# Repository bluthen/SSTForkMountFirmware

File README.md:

# SST Forkmount

This repo contains the electronic designs and software for [StarSync Trackers](https://starsynctrackers.com/)
computerized forkmount equatorial mounts. It was designed to work with SST hardware but should work with any fork mount
that uses steppers for motors.

## Component Structure

Below it tries to describe

* Computer connects to the mount through Ethernet or Wifi and control the telescope in one of the following ways.
    * A web browser [SST Discovery Tool](https://github.com/bluthen/SSTForkMountDiscovery)
    * software capable of communicating through a LX200 protocol
* Handpad is a device attached through a USB cable
    * It has a GPS moduled embedded inside it that can give the telescope accurate time and location.
    * Has a interface to control the telescope without a computer attached, with goto and manual slew functions.
* Raspberry pi has a controller board (Pi Hat) attached to it and has three main components.
    * Flask API Server - Provides a REST like API to control the telescope
    * React MUI Frontend - web based user interface to communcate with the API Server
    * LX200 Compatible TCPIP Server - An alternative way to control the telescope through a dedicated TCP/IP Port.
* Motor Control Chain
    * Microcontroller (Teensy) - The Raspberry pi has a controller board attached and communicates with it through TTL
      Serial.
    * The Microcontroller (Teensy) - communicates with stepper drivers using SPI Protocol and step/direction protocol.
    * The stepper drivers (TMC5160) - controls the RA/Dec steppers to point the telescope

# Project directory structure

* [electronics](electronics) - Files related to the hardware of: Handpad, serial to ethernet, main controller
    * [enclosures](electronics/enclosures) - Enclosures to house electronics
    * [firmware](electronics/firmware) - Microcontroller firmware
    * [pcb](electronics/pcb) - Schematic and PCB files
* [piside](piside) - Software the run on the Pi.
    * [client_advanced_slew_limits](piside/client_advanced_slew_limits) - Slew limits UI component
    * [client_main](pisiude/client_main) - The Material UI web client
    * [server](piside/server) - Flask API Server

# TODOs

* Improve a test Error modeling
    * Add Star Alignment to handpad that uses the error modeling feature
    * Good prompts for error modeling/alignment to web ui
* Script and instructions to generate object and city elevation database `ssteq.sqlite`
* More python type-hinting
* Switch from Flask to [FastAPI](https://fastapi.tiangolo.com/)
* Cleanup files piside/server in director submodules
* Better testing of encoder usage
* Easier pi setup
* Instructions for settings.json for docker usage
* Alt/Az Mode

# Screenshots

Screen shots of the web client.

# Related projects

If you are interested in this project, some of these other open source projects might interest you.

* [OnStep](https://github.com/hjd1964/OnStep)
* [AstroEQ](https://www.astroeq.co.uk/)
* [TeenAstro](https://groups.io/g/TeenAstro)

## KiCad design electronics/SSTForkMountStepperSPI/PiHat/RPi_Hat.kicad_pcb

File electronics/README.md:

# SST Electronics Hardware

## PiHat/SSTFork Stepper Micro

This is the electronics that take communication from the Pi and control the stepper motors.

## Handpad

This is the electronics of the handpad. A handheld device, with a display, to control the telescope mount.

## Serial to Ethernet

This is a small device that creates a serial port on the host computer and sends back and forth all communication on the
serial port to a IP_ADDRESS:Port through Ethernet.

This could be handy for older software that can only communicate with LX200 Protocol through a serial port.

**Computer** <-USB Serial-> **serial_to_ethernet** <-Ethernet-> **Device/Fork Mount**

# Directroy Structure

See each section for more information.

* [enclosures](enclosures) - Enclosure to house electronics
* [firmware](firmware) - Microcontroller firmware files
* [pcb](pcb) - Schematic and PCB for electronics

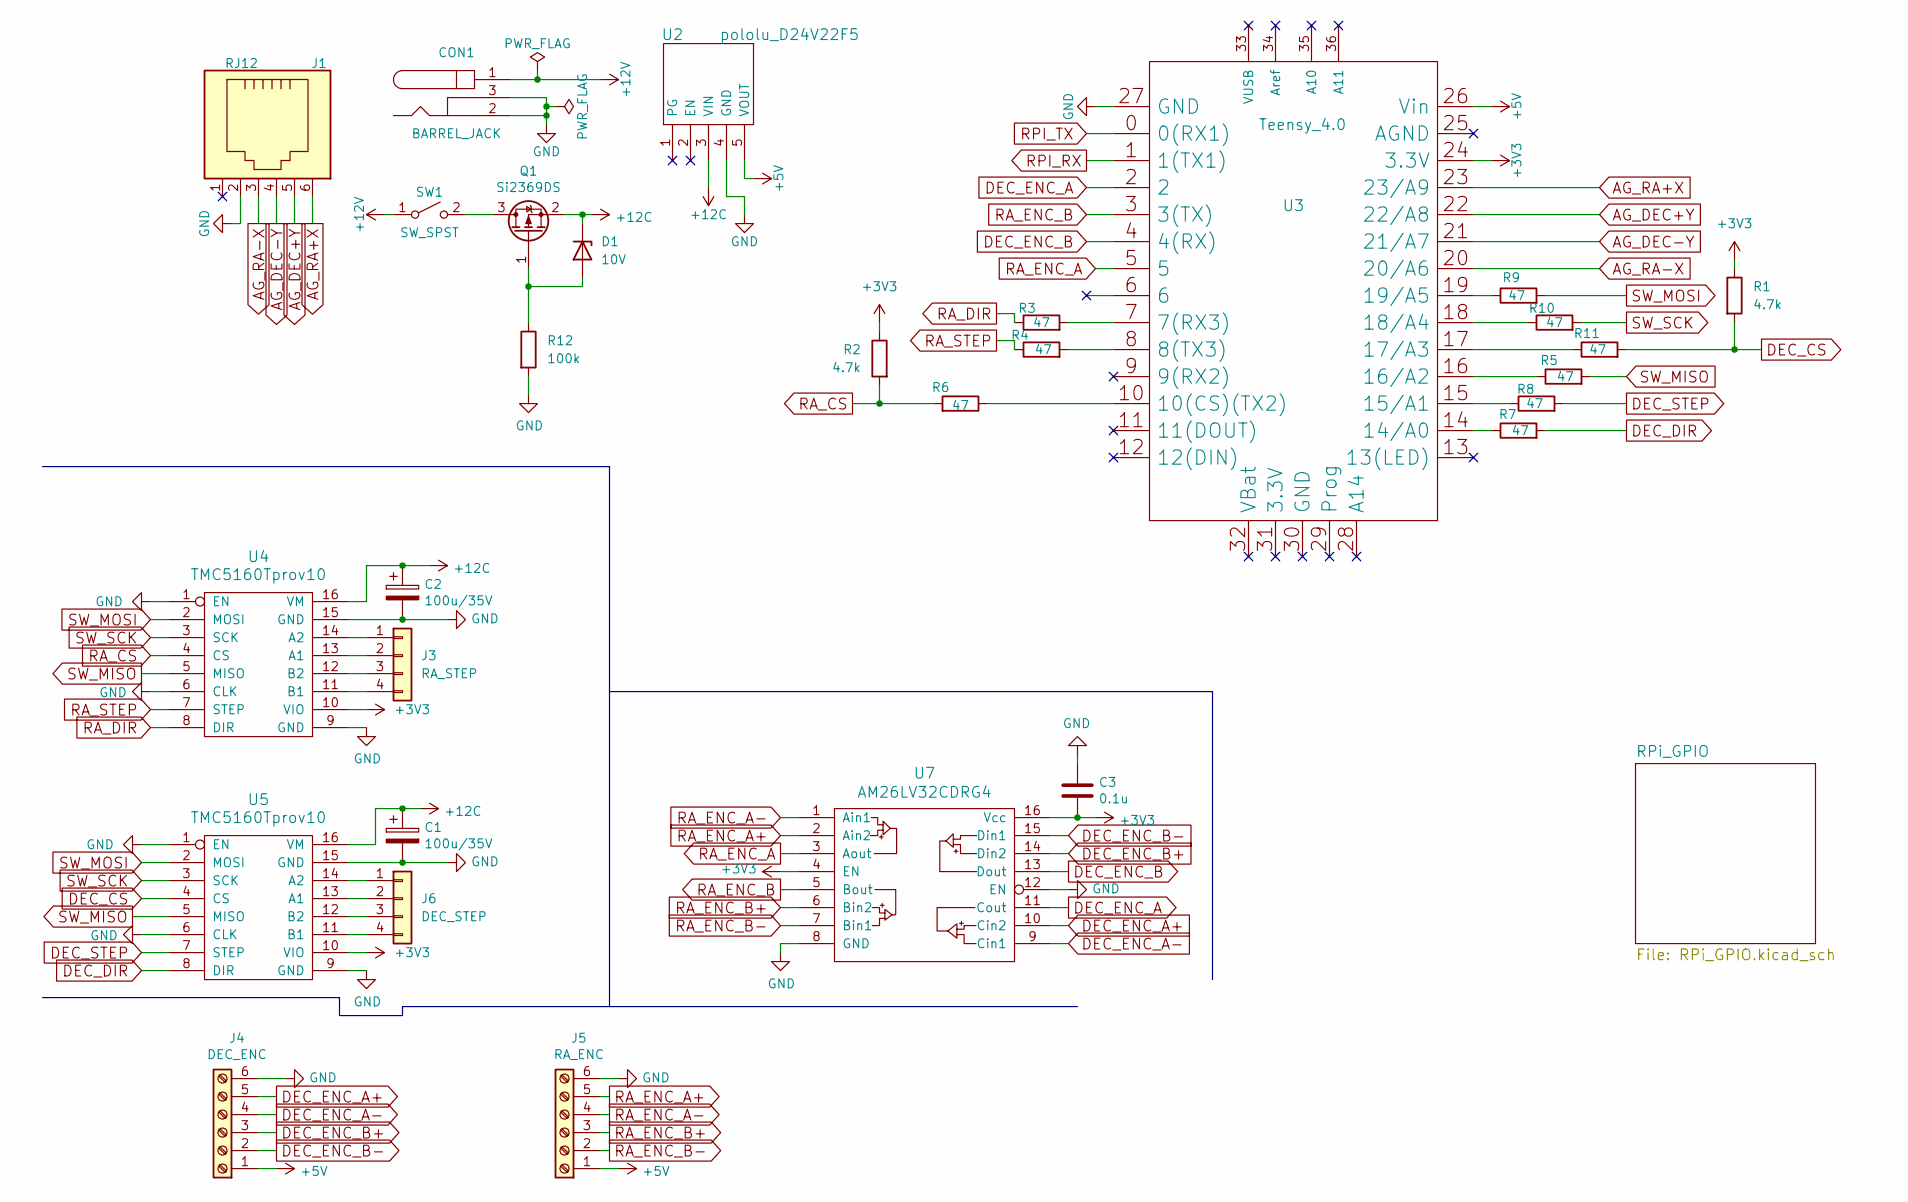
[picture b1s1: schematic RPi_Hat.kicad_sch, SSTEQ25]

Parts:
C1, C2: 100u/35V; CP_Radial_D6.3mm_P2.50mm
C3: 0.1u; C_0603
CON1: BARREL_JACK; POWER_JACK_PTH
D1: 10V; D_SOD-123
J1: RJ12; RJ11-6
J3: RA_STEP; JST_XH_B4B-XH-A_1x04_P2.50mm_Vertical
J4: DEC_ENC; JST_XH_B6B-XH-A_1x06_P2.50mm_Vertical
J5: RA_ENC; JST_XH_B6B-XH-A_1x06_P2.50mm_Vertical
J6: DEC_STEP; JST_XH_B4B-XH-A_1x04_P2.50mm_Vertical
Q1: Si2369DS; SOT-23
R1, R2: 4.7k; R_0603_1608Metric
R3, R4, R5, R6, R7, R8, R9, R10, R11: 47; R_0603_1608Metric
R12: 100k; R_0603_1608Metric
SW1: SW_SPST; PWR_SWITCH_RA1H1C112R
U2: pololu_D24V22F5
U3: Teensy_4.0; Teensy-3.1
U4, U5: TMC5160Tprov10; pololu_a4988
U7: AM26LV32CDRG4; SOIC-16_3.9x9.9mm_Pitch1.27mm

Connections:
+3V3: C3.2, R1.1, R2.1, U3.24 (3.3V), U4.10 (VIO), U5.10 (VIO), U7.4 (EN), U7.16 (Vcc)
+5V: J4.1, J5.1, U2.5 (VOUT), U3.26 (Vin); also elsewhere on the board
+12C: C1.1, C2.1, D1.1 (K), Q1.2 (S), U2.3 (VIN), U4.16 (VM), U5.16 (VM)
+12V: CON1.1, SW1.1 (A)
AG_DEC+Y: J1.5, U3.22 (22/A8)
AG_DEC-Y: J1.4, U3.21 (21/A7)
AG_RA+X: J1.6, U3.23 (23/A9)
AG_RA-X: J1.3, U3.20 (20/A6)
DEC_CS: R1.2, R11.2, U5.4 (CS)
DEC_DIR: R7.2, U5.8 (DIR)
DEC_ENC_A: U3.2, U7.11 (Cout)
DEC_ENC_A+: J4.5, U7.10 (Cin2)
DEC_ENC_A-: J4.4, U7.9 (Cin1)
DEC_ENC_B: U3.4 (4(RX)), U7.13 (Dout)
DEC_ENC_B+: J4.3, U7.14 (Din2)
DEC_ENC_B-: J4.2, U7.15 (Din1)
DEC_STEP: R8.2, U5.7 (STEP)
GND: C1.2, C2.2, C3.1, CON1.2, CON1.3, J1.2, J4.6, J5.6, R12.2, U2.4 (GND), U3.27 (GND), U4.1 (EN), U4.6 (CLK), U4.9 (GND), U4.15 (GND), U5.1 (EN), U5.6 (CLK), U5.9 (GND), U5.15 (GND), U7.8 (GND), U7.12 (EN); also elsewhere on the board
unnamed: D1.2 (A), Q1.1 (G), R12.1
unnamed: J3.1, U4.14 (A2)
unnamed: J3.2, U4.13 (A1)
unnamed: J3.3, U4.12 (B2)
unnamed: J3.4, U4.11 (B1)
unnamed: J6.1, U5.14 (A2)
unnamed: J6.2, U5.13 (A1)
unnamed: J6.3, U5.12 (B2)
unnamed: J6.4, U5.11 (B1)
unnamed: Q1.3 (D), SW1.2 (B)
unnamed: R3.2, U3.7 (7(RX3))
unnamed: R4.2, U3.8 (8(TX3))
unnamed: R6.1, U3.10 (10(CS)(TX2))
unnamed: R7.1, U3.14 (14/A0)
unnamed: R8.1, U3.15 (15/A1)
unnamed: R5.1, U3.16 (16/A2)
unnamed: R11.1, U3.17 (17/A3)
unnamed: R10.1, U3.18 (18/A4)
unnamed: R9.1, U3.19 (19/A5)
RA_CS: R2.2, R6.2, U4.4 (CS)
RA_DIR: R3.1, U4.8 (DIR)
RA_ENC_A: U3.5, U7.3 (Aout)
RA_ENC_A+: J5.5, U7.2 (Ain2)
RA_ENC_A-: J5.4, U7.1 (Ain1)
RA_ENC_B: U3.3 (3(TX)), U7.5 (Bout)
RA_ENC_B+: J5.3, U7.6 (Bin2)
RA_ENC_B-: J5.2, U7.7 (Bin1)
RA_STEP: R4.1, U4.7 (STEP)
RPI_RX: U3.1 (1(TX1)); also elsewhere on the board
RPI_TX: U3.0 (0(RX1)); also elsewhere on the board
SW_MISO: R5.2, U4.5 (MISO), U5.5 (MISO)
SW_MOSI: R9.2, U4.2 (MOSI), U5.2 (MOSI)
SW_SCK: R10.2, U4.3 (SCK), U5.3 (SCK)

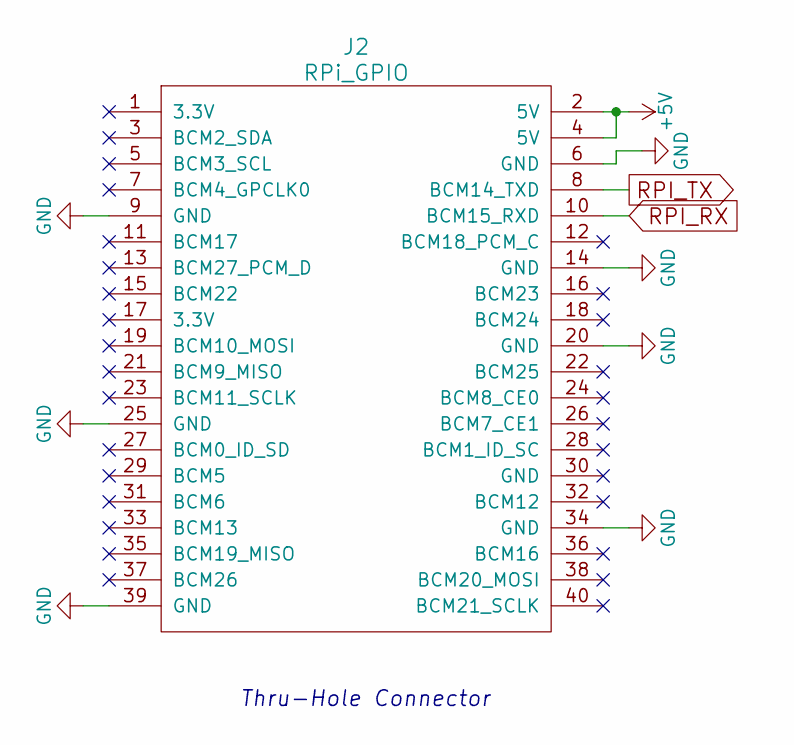
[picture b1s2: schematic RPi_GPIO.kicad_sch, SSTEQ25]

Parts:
J2: RPi_GPIO; Pin_Header_Straight_2x20

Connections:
+5V: J2.2 (5V), J2.4 (5V); also elsewhere on the board
GND: J2.6 (GND), J2.9 (GND), J2.14 (GND), J2.20 (GND), J2.25 (GND), J2.34 (GND), J2.39 (GND); also elsewhere on the board
RPI_RX: J2.10 (BCM15_RXD); also elsewhere on the board
RPI_TX: J2.8 (BCM14_TXD); also elsewhere on the board

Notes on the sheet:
Thru-Hole Connector

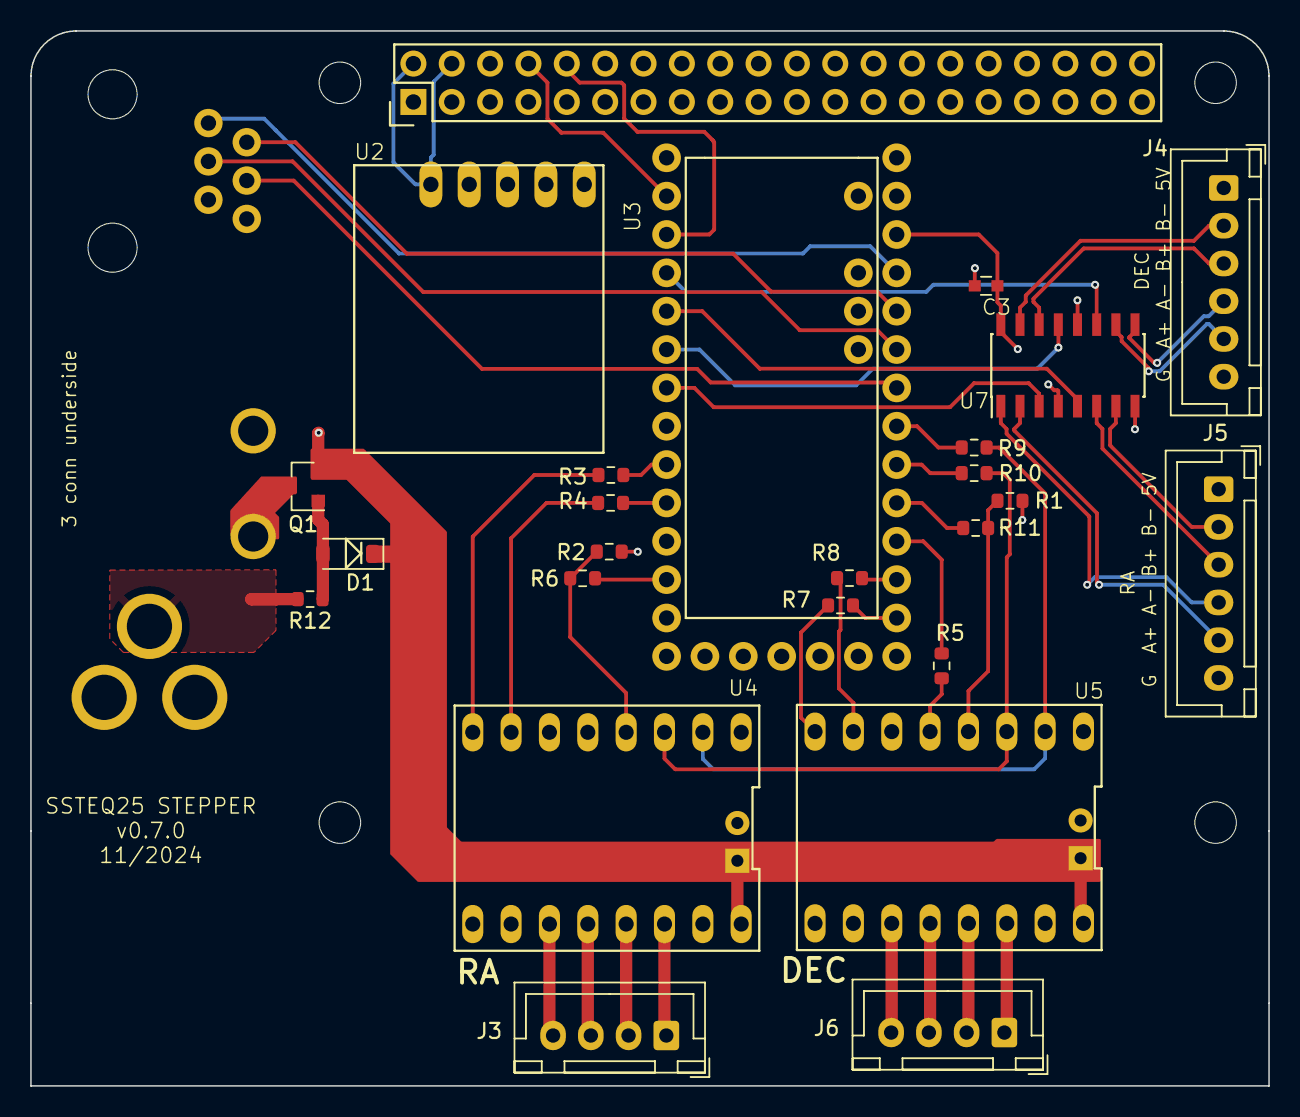
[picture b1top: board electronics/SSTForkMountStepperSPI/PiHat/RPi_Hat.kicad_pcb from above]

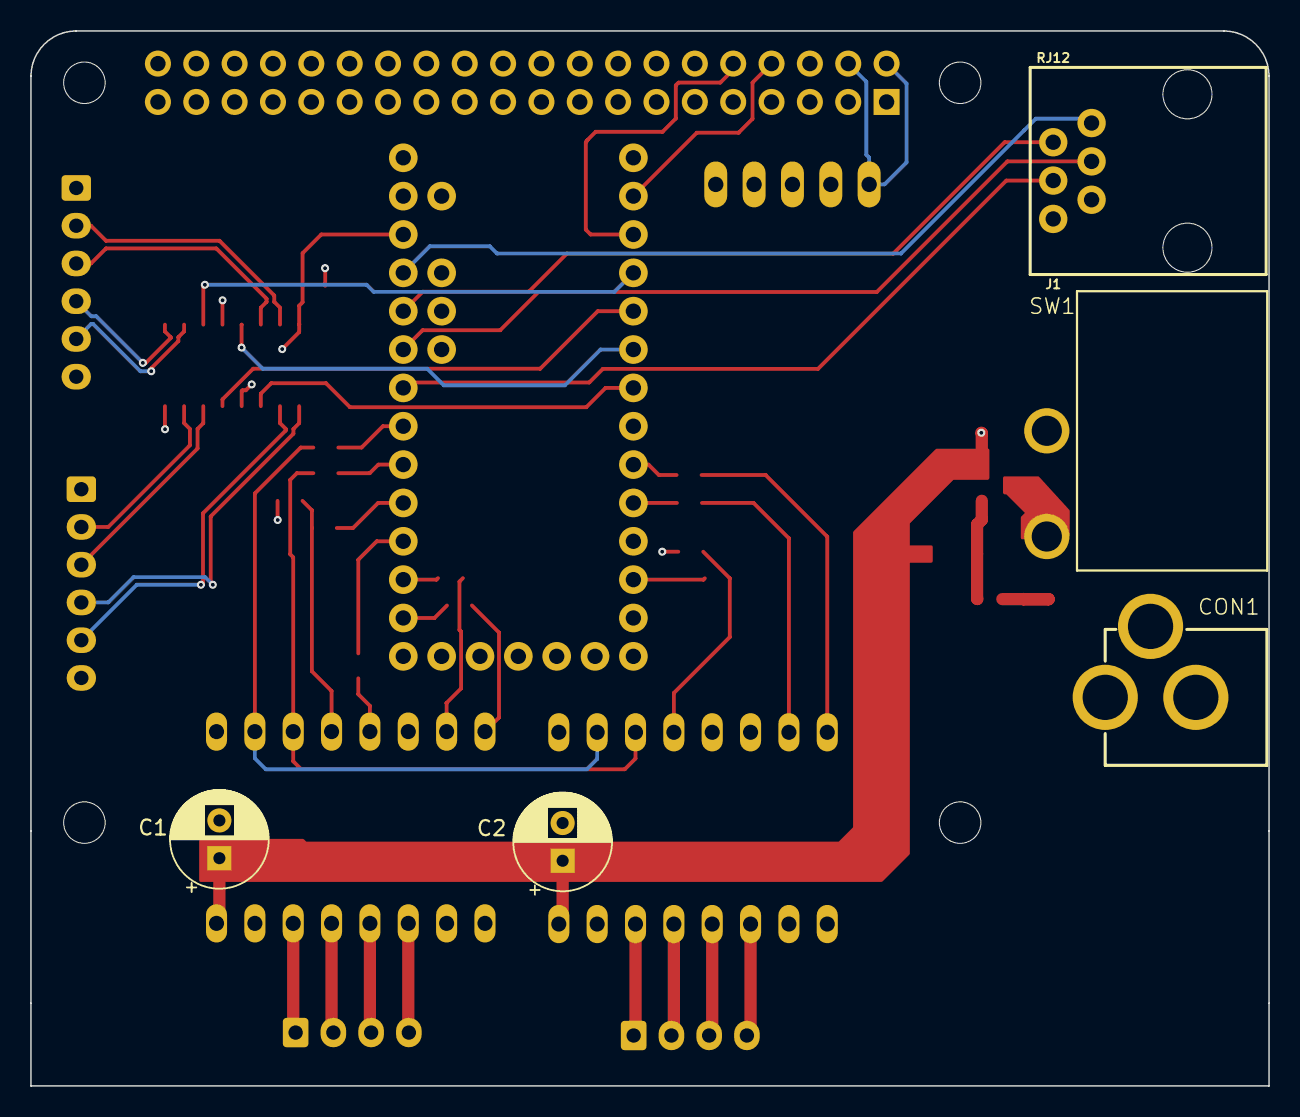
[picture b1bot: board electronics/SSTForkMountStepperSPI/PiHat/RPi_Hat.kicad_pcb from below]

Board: 4 copper layers, 82.0 x 69.9 mm, 30 parts (5 on the bottom side), 51 nets.

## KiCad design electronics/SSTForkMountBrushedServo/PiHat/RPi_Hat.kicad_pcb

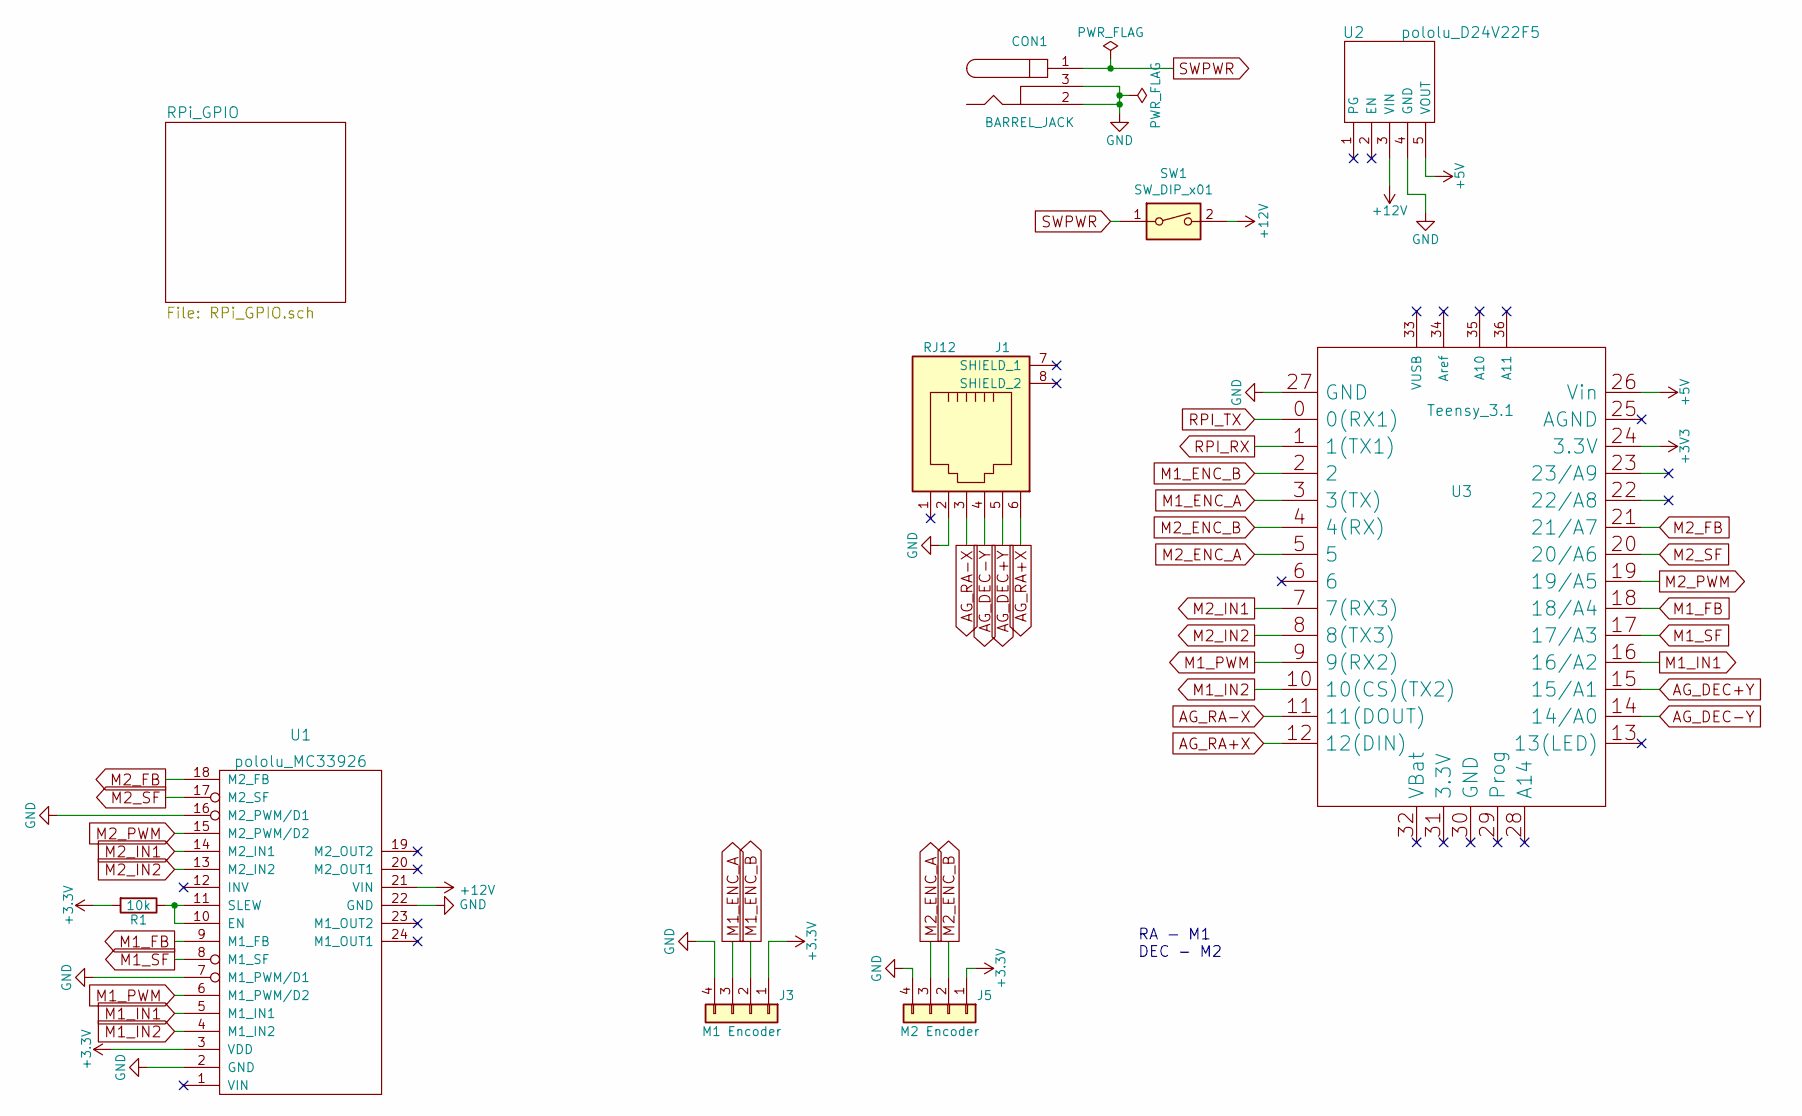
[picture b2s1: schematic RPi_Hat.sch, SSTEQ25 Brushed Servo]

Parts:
CON1: BARREL_JACK; POWER_JACK_PTH
J1: RJ12; RJ11-6
J3: M1 Encoder; 1X04_LOCK_LONGPADS
J5: M2 Encoder; 1X04_LOCK_LONGPADS
R1: 10k; R_0603
SW1: SW_DIP_x01; PWR_SWITCH_RA1H1C112R
U1: pololu_MC33926; pololu_mc33926
U2: pololu_D24V22F5
U3: Teensy_3.1; Teensy-3.1

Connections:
+5V: U2.5 (VOUT), U3.26 (Vin); also elsewhere on the board
+12V: SW1.2, U1.21 (VIN), U2.3 (VIN)
AG_DEC+Y: J1.5, U3.15 (15/A1)
AG_DEC-Y: J1.4, U3.14 (14/A0)
AG_RA+X: J1.6, U3.12 (12(DIN))
AG_RA-X: J1.3, U3.11 (11(DOUT))
GND: CON1.2, CON1.3, J1.2, J3.4, J5.4, U1.2 (GND), U1.7 (M1_PWM/D1), U1.16 (M2_PWM/D1), U1.22 (GND), U2.4 (GND), U3.27 (GND); also elsewhere on the board
M1_ENC_A: J3.3, U3.3 (3(TX))
M1_ENC_B: J3.2, U3.2
M1_FB: U1.9 (M1_FB), U3.18 (18/A4)
M1_IN1: U1.5 (M1_IN1), U3.16 (16/A2)
M1_IN2: U1.4 (M1_IN2), U3.10 (10(CS)(TX2))
M1_PWM: U1.6 (M1_PWM/D2), U3.9 (9(RX2))
M1_SF: U1.8 (M1_SF), U3.17 (17/A3)
M2_ENC_A: J5.3, U3.5
M2_ENC_B: J5.2, U3.4 (4(RX))
M2_FB: U1.18 (M2_FB), U3.21 (21/A7)
M2_IN1: U1.14 (M2_IN1), U3.7 (7(RX3))
M2_IN2: U1.13 (M2_IN2), U3.8 (8(TX3))
M2_PWM: U1.15 (M2_PWM/D2), U3.19 (19/A5)
M2_SF: U1.17 (M2_SF), U3.20 (20/A6)
unnamed: R1.1, U1.10 (EN), U1.11 (SLEW)
RPI_RX: U3.1 (1(TX1)); also elsewhere on the board
RPI_TX: U3.0 (0(RX1)); also elsewhere on the board
SWPWR: CON1.1, SW1.1

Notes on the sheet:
RA - M1 DEC - M2

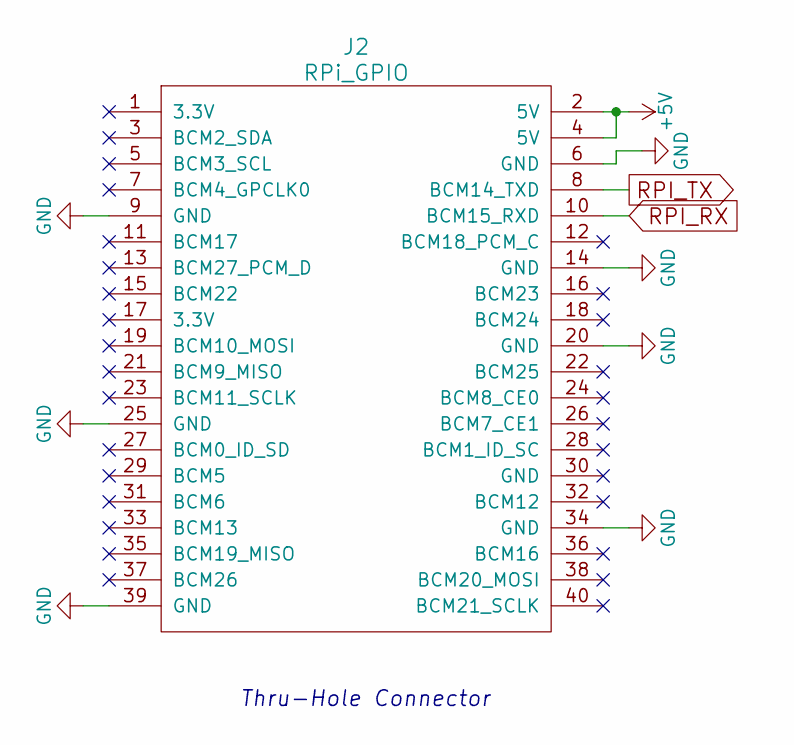
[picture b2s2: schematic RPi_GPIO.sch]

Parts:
J2: RPi_GPIO; Pin_Header_Straight_2x20

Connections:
+5V: J2.2 (5V), J2.4 (5V); also elsewhere on the board
GND: J2.6 (GND), J2.9 (GND), J2.14 (GND), J2.20 (GND), J2.25 (GND), J2.34 (GND), J2.39 (GND); also elsewhere on the board
RPI_RX: J2.10 (BCM15_RXD); also elsewhere on the board
RPI_TX: J2.8 (BCM14_TXD); also elsewhere on the board

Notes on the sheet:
Thru-Hole Connector

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
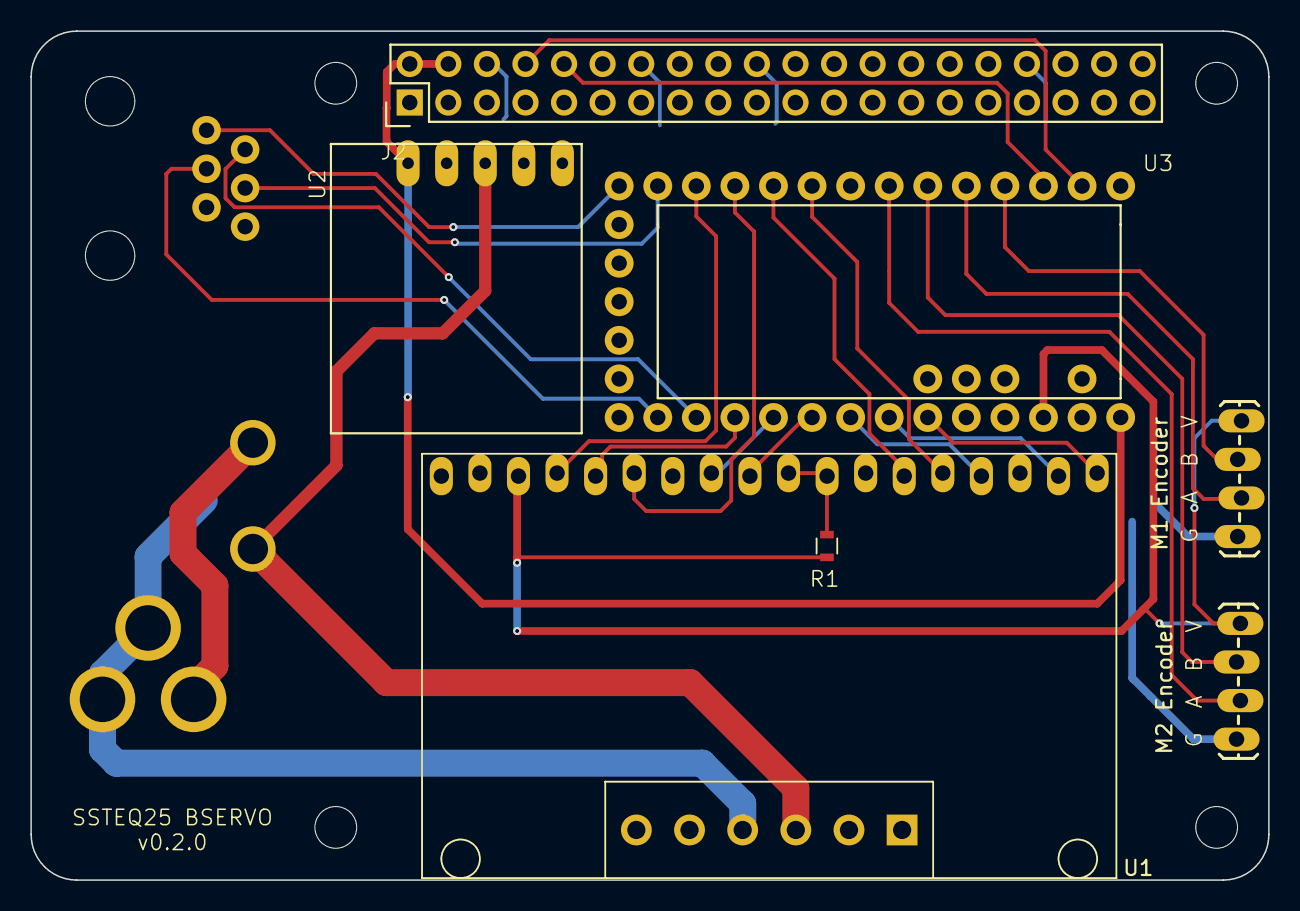
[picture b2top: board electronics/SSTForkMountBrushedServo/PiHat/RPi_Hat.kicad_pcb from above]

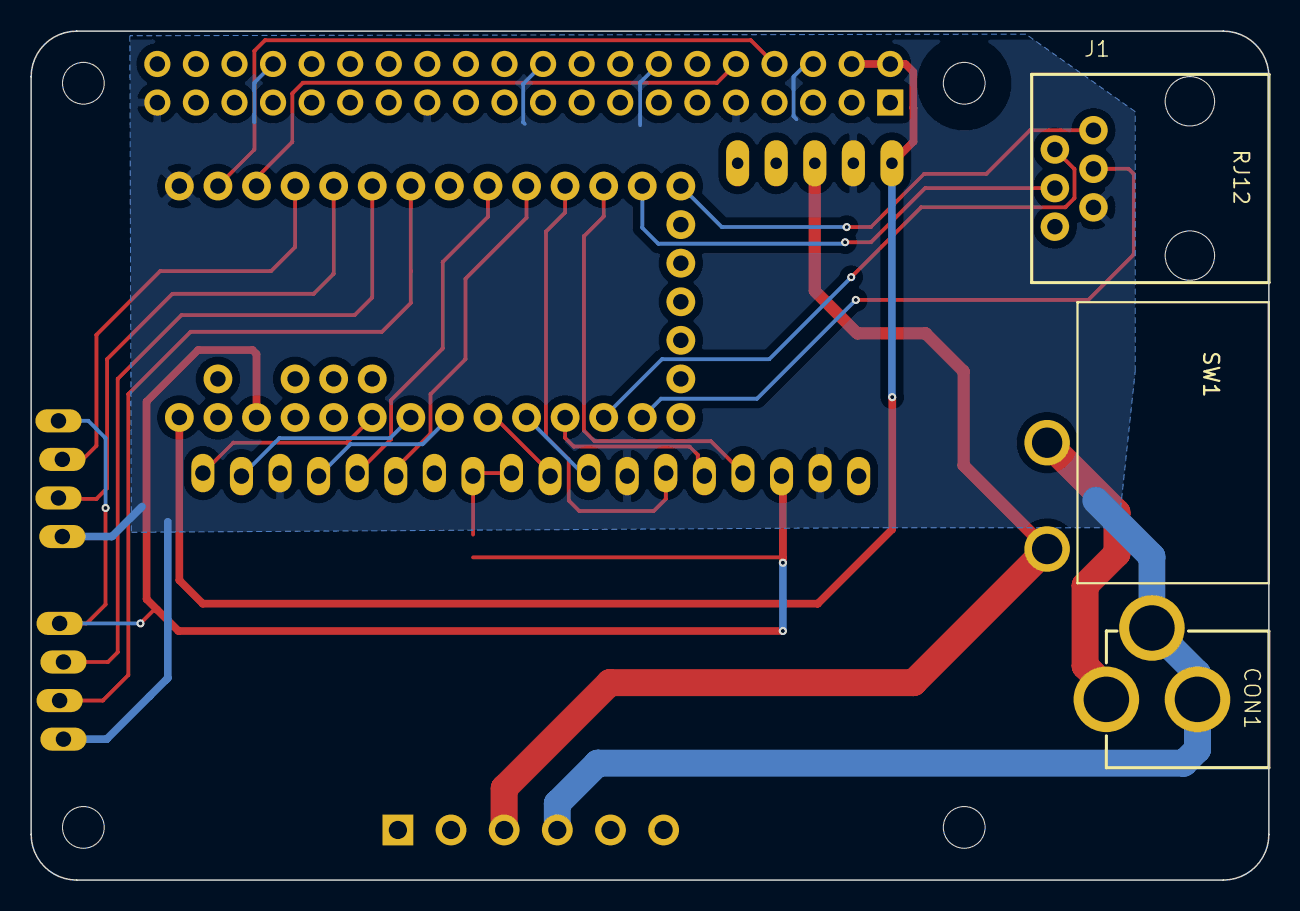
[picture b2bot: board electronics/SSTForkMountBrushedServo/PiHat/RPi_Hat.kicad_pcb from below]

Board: 2 copper layers, 81.5 x 55.9 mm, 10 parts (3 on the bottom side), 26 nets.

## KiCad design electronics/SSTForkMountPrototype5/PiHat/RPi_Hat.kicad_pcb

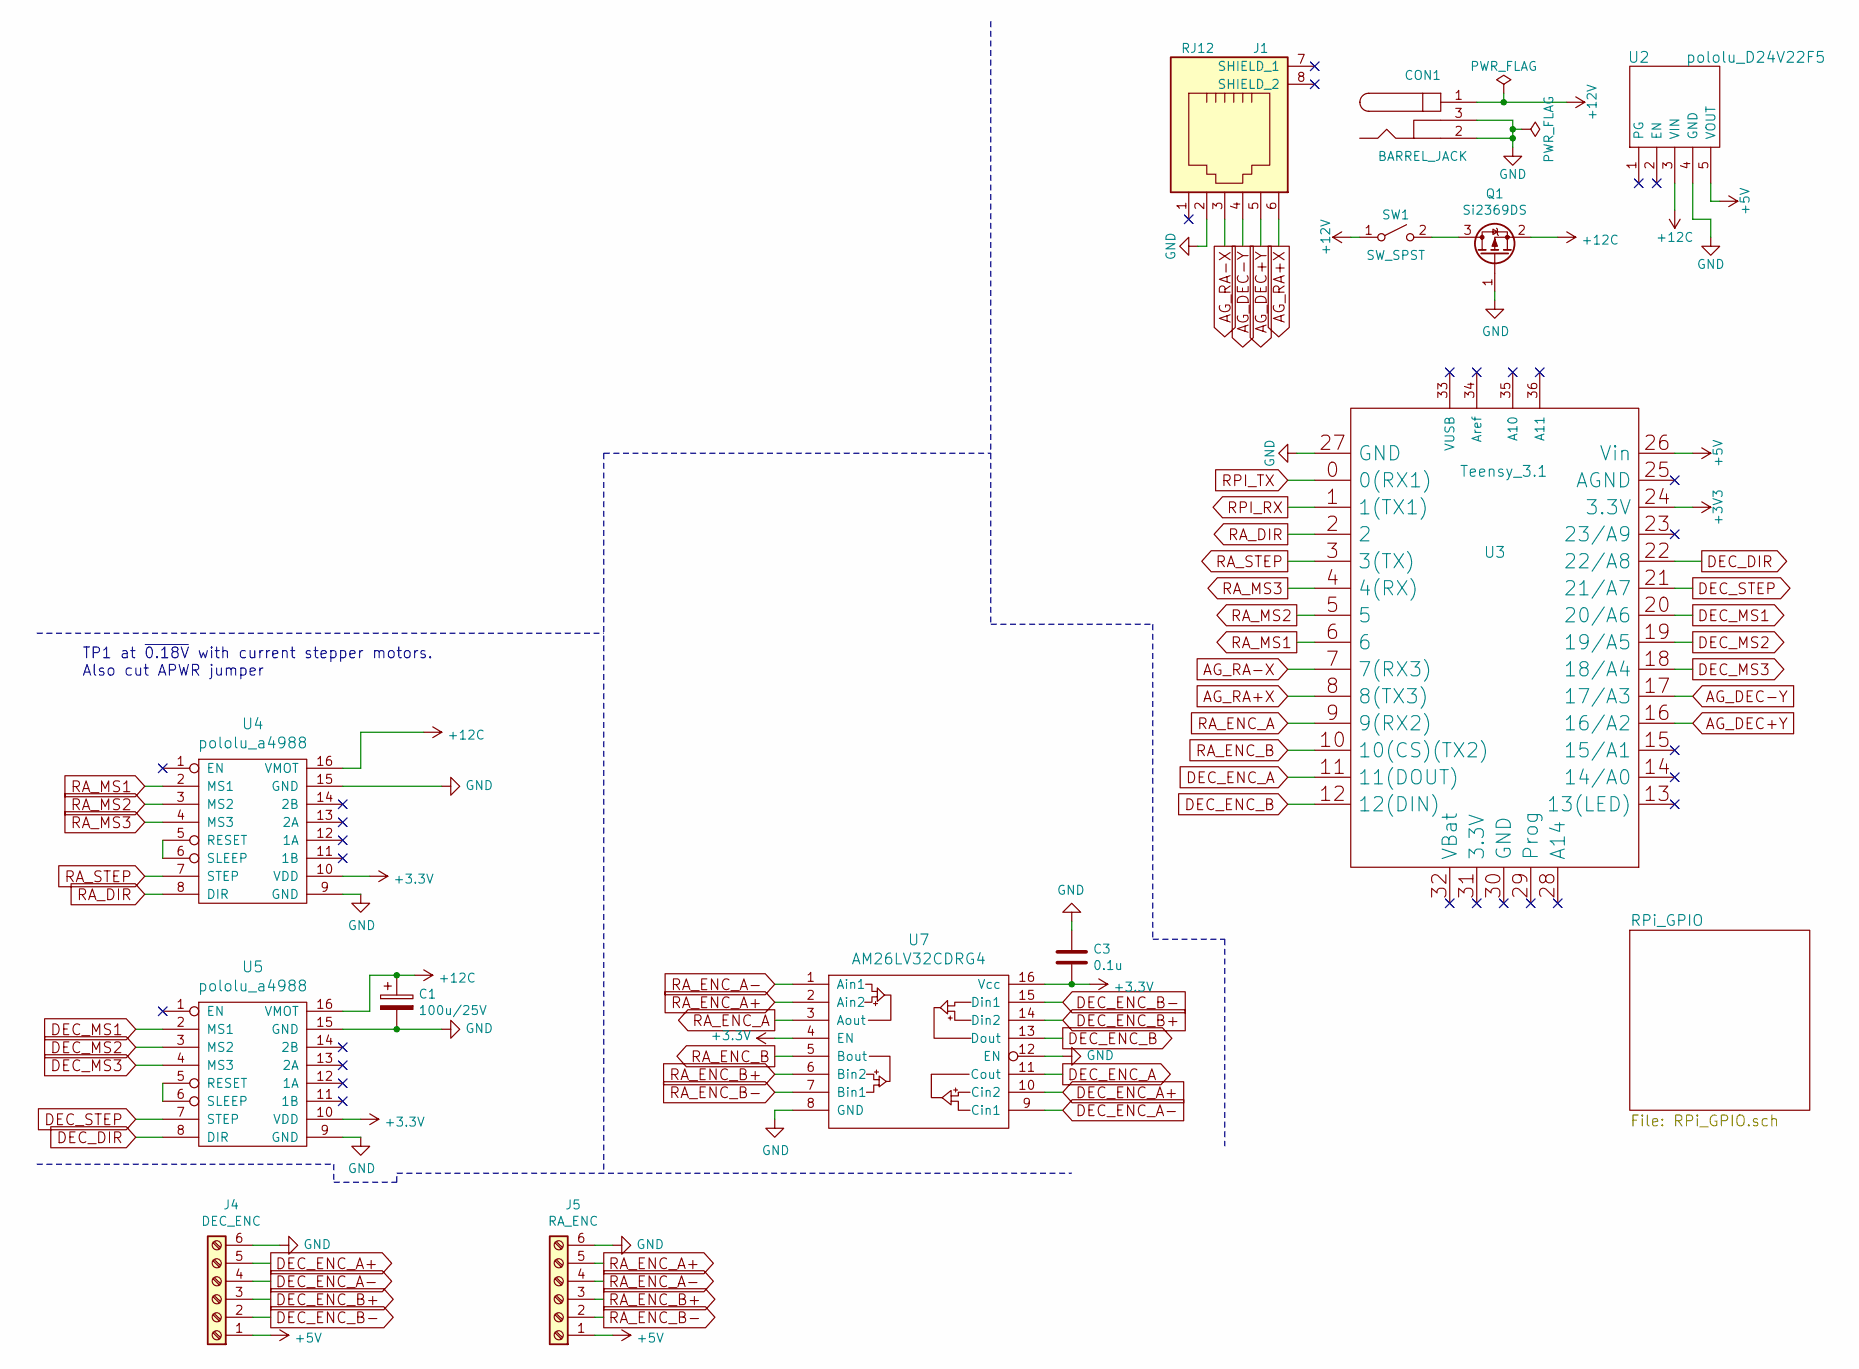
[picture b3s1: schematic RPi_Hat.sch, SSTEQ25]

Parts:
C1: 100u/25V; CP_Elec_8x5.4
C3: 0.1u; C_0603
CON1: BARREL_JACK; POWER_JACK_PTH
J1: RJ12; RJ11-6
J4: DEC_ENC; 1X06_LOCK_LONGPADS
J5: RA_ENC; 1X06_LOCK_LONGPADS
Q1: Si2369DS; SOT-23
SW1: SW_SPST; PWR_SWITCH_RA1H1C112R
U2: pololu_D24V22F5
U3: Teensy_3.1; Teensy-3.1
U4, U5: pololu_a4988
U7: AM26LV32CDRG4; SOIC-16_3.9x9.9mm_Pitch1.27mm

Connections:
+5V: J4.1, J5.1, U2.5 (VOUT), U3.26 (Vin); also elsewhere on the board
+12C: C1.1, Q1.2 (S), U2.3 (VIN), U4.16 (VMOT), U5.16 (VMOT)
+12V: CON1.1, SW1.1 (A)
AG_DEC+Y: J1.5, U3.16 (16/A2)
AG_DEC-Y: J1.4, U3.17 (17/A3)
AG_RA+X: J1.6, U3.8 (8(TX3))
AG_RA-X: J1.3, U3.7 (7(RX3))
DEC_DIR: U3.22 (22/A8), U5.8 (DIR)
DEC_ENC_A: U3.11 (11(DOUT)), U7.11 (Cout)
DEC_ENC_A+: J4.5, U7.10 (Cin2)
DEC_ENC_A-: J4.4, U7.9 (Cin1)
DEC_ENC_B: U3.12 (12(DIN)), U7.13 (Dout)
DEC_ENC_B+: J4.3, U7.14 (Din2)
DEC_ENC_B-: J4.2, U7.15 (Din1)
DEC_MS1: U3.20 (20/A6), U5.2 (MS1)
DEC_MS2: U3.19 (19/A5), U5.3 (MS2)
DEC_MS3: U3.18 (18/A4), U5.4 (MS3)
DEC_STEP: U3.21 (21/A7), U5.7 (STEP)
GND: C1.2, C3.1, CON1.2, CON1.3, J1.2, J4.6, J5.6, Q1.1 (G), U2.4 (GND), U3.27 (GND), U4.9 (GND), U4.15 (GND), U5.9 (GND), U5.15 (GND), U7.8 (GND), U7.12 (EN); also elsewhere on the board
unnamed: Q1.3 (D), SW1.2 (B)
unnamed: U4.5 (RESET), U4.6 (SLEEP)
unnamed: U5.5 (RESET), U5.6 (SLEEP)
RA_DIR: U3.2, U4.8 (DIR)
RA_ENC_A: U3.9 (9(RX2)), U7.3 (Aout)
RA_ENC_A+: J5.5, U7.2 (Ain2)
RA_ENC_A-: J5.4, U7.1 (Ain1)
RA_ENC_B: U3.10 (10(CS)(TX2)), U7.5 (Bout)
RA_ENC_B+: J5.3, U7.6 (Bin2)
RA_ENC_B-: J5.2, U7.7 (Bin1)
RA_MS1: U3.6, U4.2 (MS1)
RA_MS2: U3.5, U4.3 (MS2)
RA_MS3: U3.4 (4(RX)), U4.4 (MS3)
RA_STEP: U3.3 (3(TX)), U4.7 (STEP)
RPI_RX: U3.1 (1(TX1)); also elsewhere on the board
RPI_TX: U3.0 (0(RX1)); also elsewhere on the board

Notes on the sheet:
TP1 at ~0.18V with current stepper motors. Also cut APWR jumper

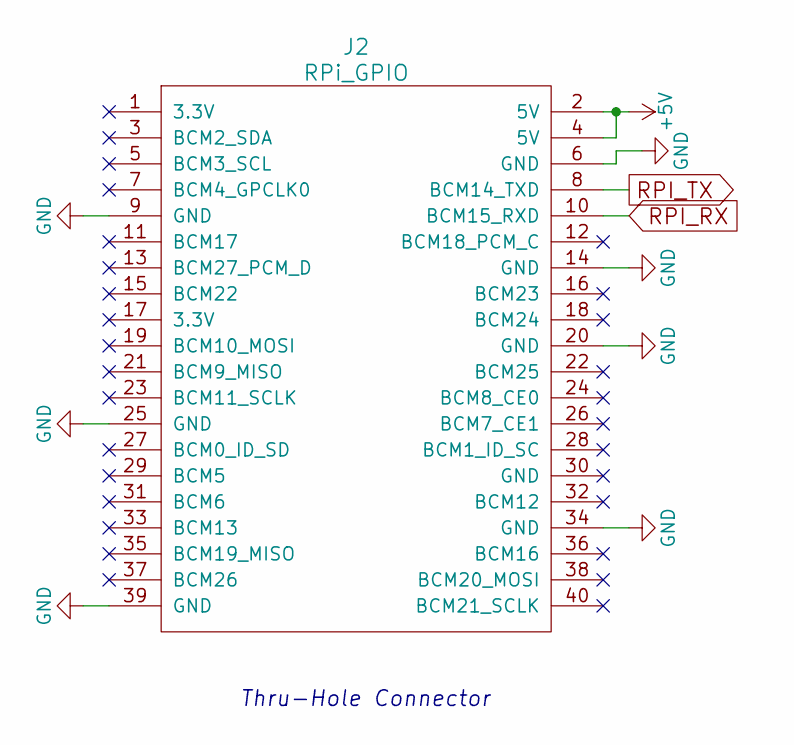
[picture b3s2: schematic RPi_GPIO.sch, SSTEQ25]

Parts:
J2: RPi_GPIO; Pin_Header_Straight_2x20

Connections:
+5V: J2.2 (5V), J2.4 (5V); also elsewhere on the board
GND: J2.6 (GND), J2.9 (GND), J2.14 (GND), J2.20 (GND), J2.25 (GND), J2.34 (GND), J2.39 (GND); also elsewhere on the board
RPI_RX: J2.10 (BCM15_RXD); also elsewhere on the board
RPI_TX: J2.8 (BCM14_TXD); also elsewhere on the board

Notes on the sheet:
Thru-Hole Connector

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
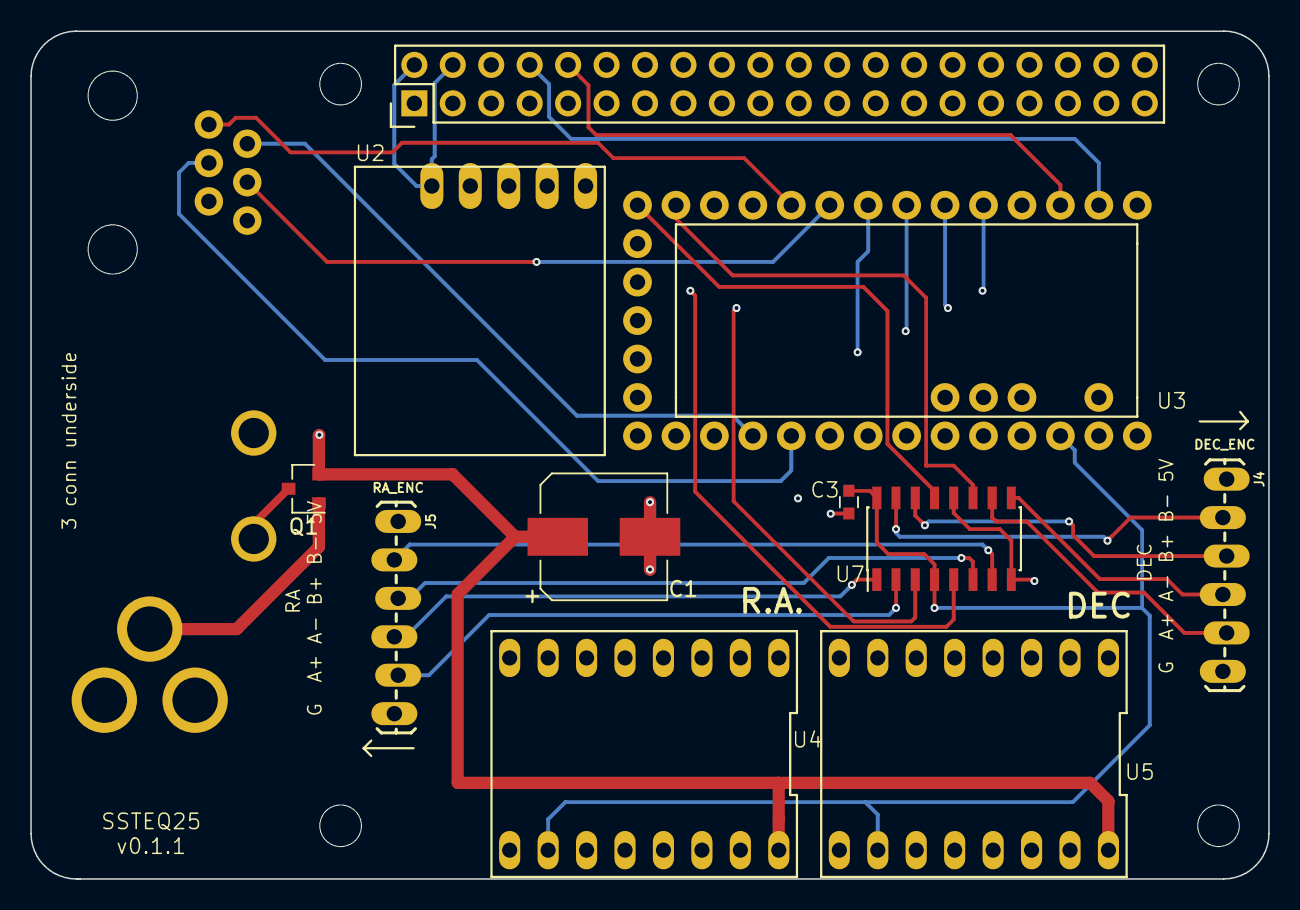
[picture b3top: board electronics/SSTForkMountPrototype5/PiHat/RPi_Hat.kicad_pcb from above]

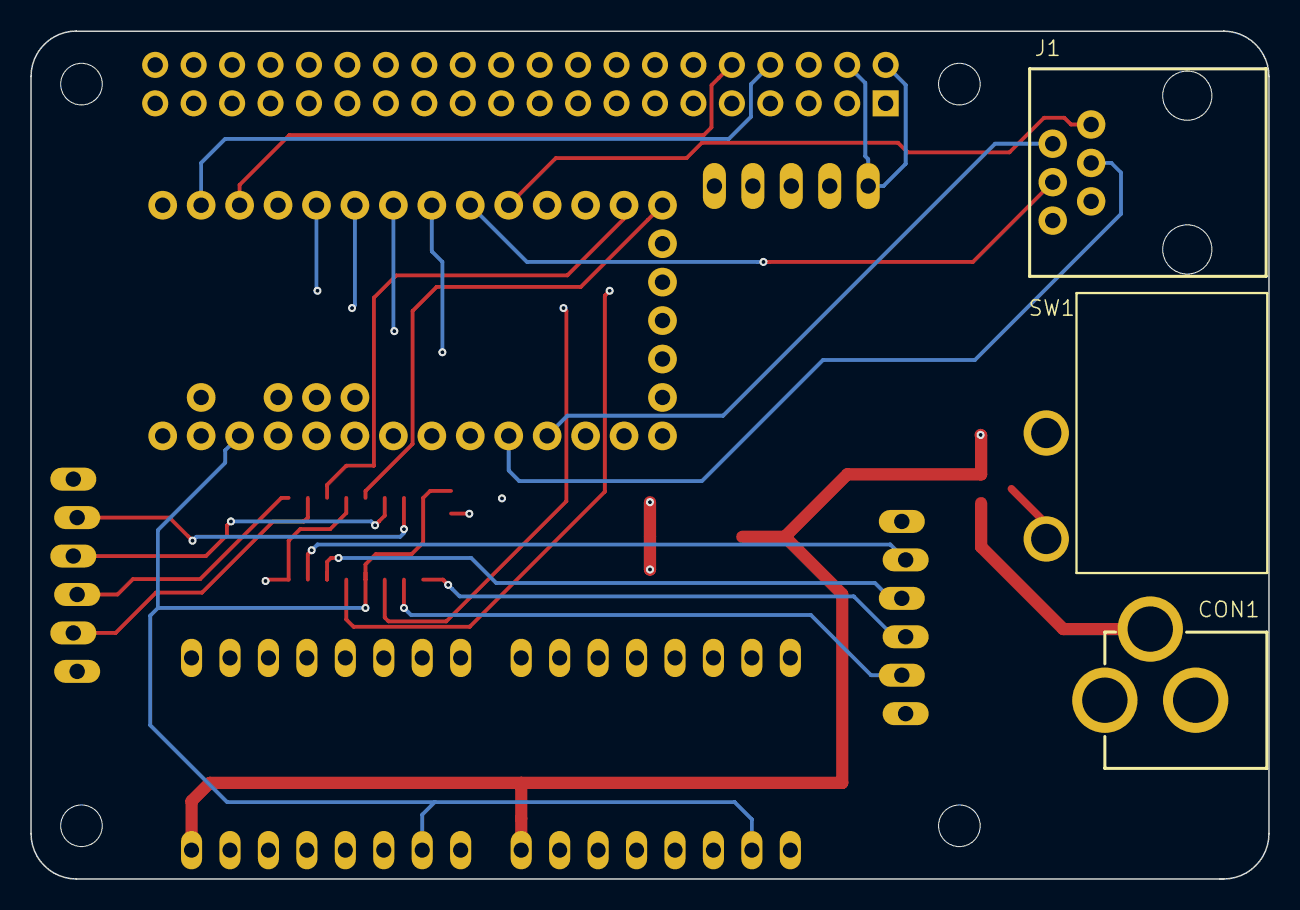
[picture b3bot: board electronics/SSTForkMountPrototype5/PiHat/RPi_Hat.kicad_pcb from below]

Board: 4 copper layers, 81.8 x 56.0 mm, 14 parts (3 on the bottom side), 36 nets.
